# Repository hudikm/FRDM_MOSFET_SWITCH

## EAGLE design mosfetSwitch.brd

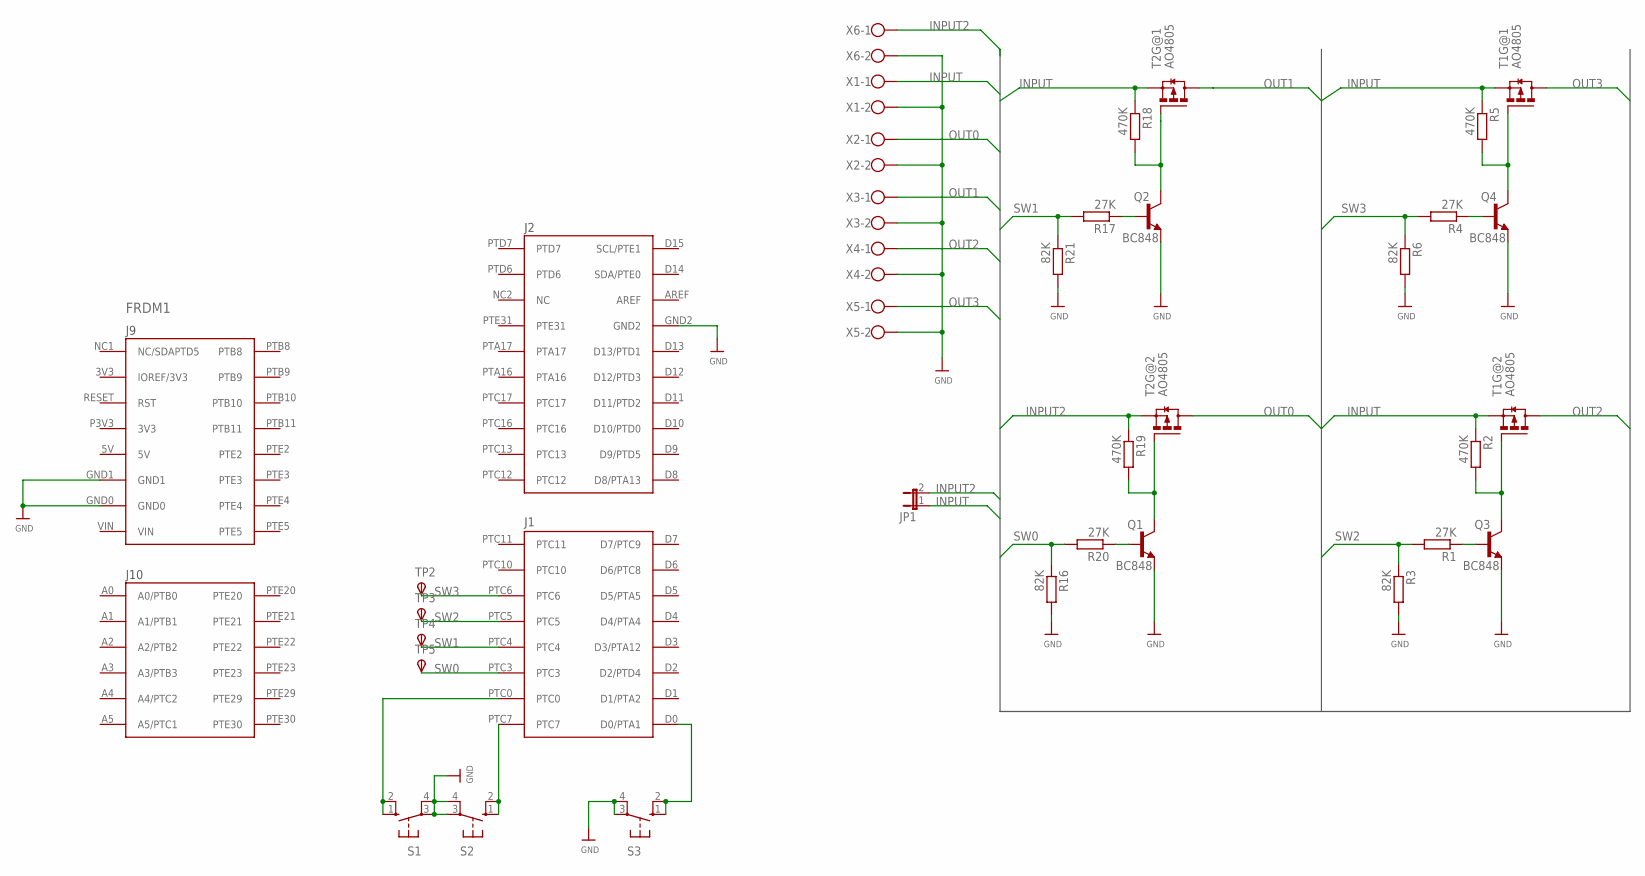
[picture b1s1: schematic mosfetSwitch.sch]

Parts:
FRDM1: FRDM-KL25ZNORMAL; FRDM_KL25Z_NORMAL
JP1: JP1E; JP1
Q1, Q2, Q3, Q4: BC848; SOT23
R1, R4, R17, R20: 27K; R0805
R2, R5, R18, R19: 470K; R0805
R3, R6, R16, R21: 82K; R0805
S1, S2, S3: 10-XX3D; B3F-10XX_2
T1, T2: AO4805; SOIC127P600X175-8
TP2, TP3, TP4, TP5: TPSB2,54; B2,54
X1, X2, X3, X4, X5, X6: W237-102

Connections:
GND: FRDM1.GND0, FRDM1.GND1, FRDM1.GND2, Q1.2 (E), Q2.2 (E), Q3.2 (E), Q4.2 (E), R3.2, R6.2, R16.2, R21.2, S1.3, S1.4 (P1), S2.3, S2.4 (P1), S3.3, S3.4 (P1), X1.2, X2.2, X3.2, X4.2, X5.2, X6.2
INPUT: JP1.1, R2.1, R5.1, R18.1, T1.1 (S), T1.3 (S), T2.3 (S), X1.1
INPUT2: JP1.2, R19.1, T2.1 (S), X6.1
unnamed: Q3.1 (B), R1.1
unnamed: Q3.3 (C), R2.2, T1.2 (G)
unnamed: Q2.1 (B), R17.1
unnamed: Q2.3 (C), R18.2, T2.4 (G)
unnamed: Q4.1 (B), R4.1
unnamed: Q4.3 (C), R5.2, T1.4 (G)
unnamed: FRDM1.PTC0, S1.1 (S), S1.2 (S1)
unnamed: FRDM1.D0 (D0/PTA1), S3.1 (S), S3.2 (S1)
unnamed: Q1.1 (B), R20.1
unnamed: FRDM1.PTC7, S2.1 (S), S2.2 (S1)
unnamed: Q1.3 (C), R19.2, T2.2 (G)
OUT0: T2.7 (D), T2.8 (D), X2.1
OUT1: T2.5 (D), T2.6 (D), X3.1
OUT2: T1.7 (D), T1.8 (D), X4.1
OUT3: T1.5 (D), T1.6 (D), X5.1
SW0: FRDM1.PTC3, R16.1, R20.2, TP5.TP
SW1: FRDM1.PTC4, R17.2, R21.1, TP4.TP
SW2: FRDM1.PTC5, R1.2, R3.1, TP3.TP
SW3: FRDM1.PTC6, R4.2, R6.1, TP2.TP

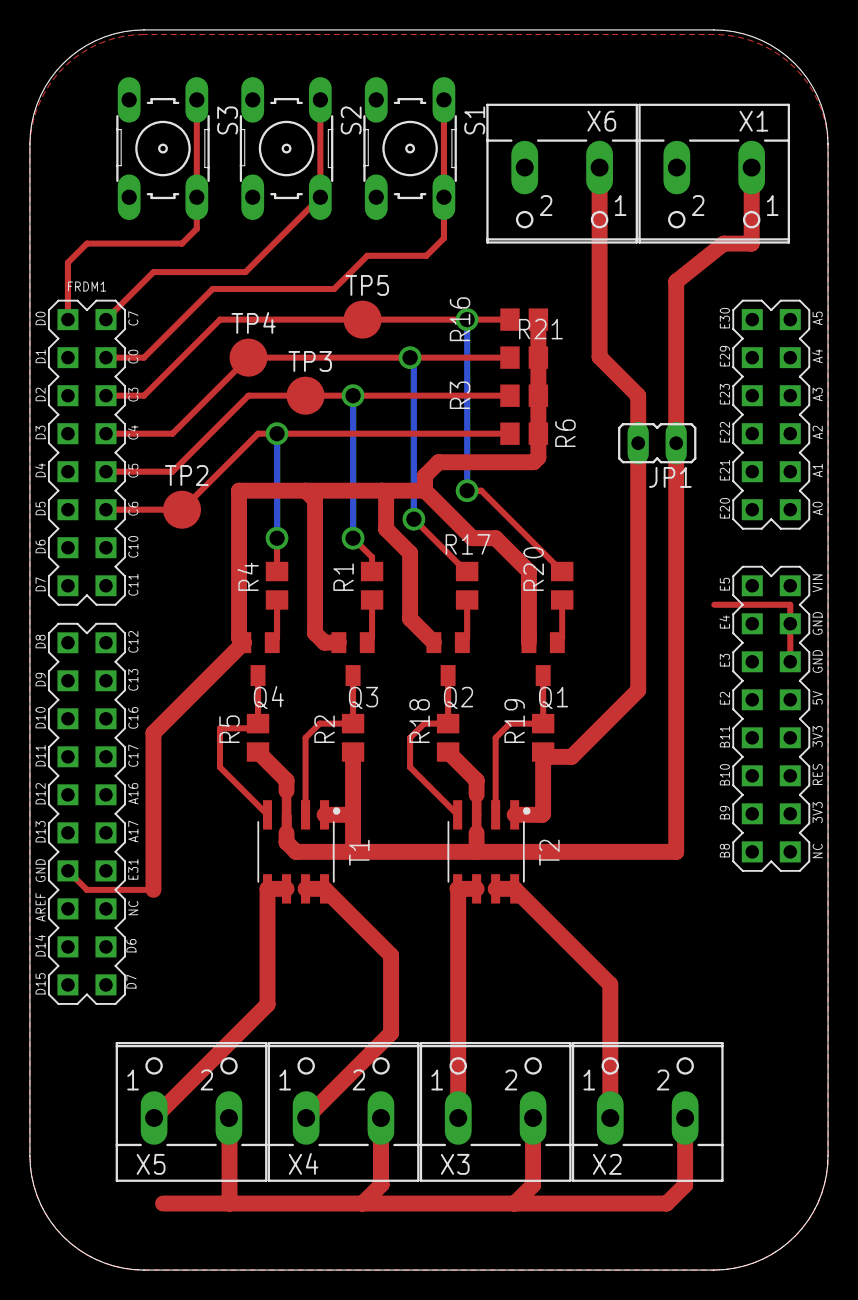
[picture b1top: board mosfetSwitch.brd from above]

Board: 2 copper layers, 53.3 x 82.9 mm, 33 parts (0 on the bottom side), 22 nets.

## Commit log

2018-11-05 Init commit
2018-11-05 BRD pridane test pady
